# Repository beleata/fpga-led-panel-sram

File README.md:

# ICND1065L LED Panel: FPGA SRAM and RP2040 Pico

64x32 ICND1065L RGB LED panel drivers: Olimex iCE40HX1K FPGA with SRAM video
memory, and a YD-RP2040 / Raspberry Pi Pico PIO + DMA display implementation
with USB frame streaming. Wiring, initialization protocol, source, tests and
ready-to-flash firmware are included.

## Custom Controller PCB (Draft)

Самостоятелна двуслойна платка **88 x 46.1 mm** с RP2040, 8 MiB flash,
вертикална USB-C, RS-485 и W5500 Ethernet с вертикална RJ45.

**НЕ Е ГОТОВА ЗА ПРОИЗВОДСТВО.** Публикувани са схемата, 103 компонента,
ръчната подредба и пробно трасиране. След корекциите: 0 DRC нарушения,
но остава 1 неопроводена връзка QSPI_D1. Сигналната цялост и захранването
още не са квалифицирани. Това не променя статуса на работещия Pico модул.

- [PCB files, current status and documentation](hardware/pico-panel/README.md)
- [Пробно трасиране и ограничения](hardware/pico-panel/routing-trial/README_BG.md)

## RP2040 Pico

Потвърден работещ вариант с **YD-RP2040 2022-V1.3, 8 MiB flash**:
правилна геометрична фигура и стабилна картина. PIO и DMA изпълняват
проверената FPGA последователност при SCLK **1.5625 MHz**.

- [Свързване, компилиране и инструкции](pico/README_BG.md)
- [Готов firmware за YD-RP2040 8 MiB](pico/pico_panel.uf2)
- [Изходен код и тестове](pico/)

Добавен е USB CDC приемник с два RGB888 буфера във вътрешната SRAM на Pico.
PC декодира GIF и изпраща кадрите; Pico пази последния кадър при спиране
на изпращането. [USB видео: инструкции и протокол](pico/USB_VIDEO_BG.md).
Новият [USB firmware](pico/pico_panel_usb.uf2) е отделен от стария статичен UF2.
Измерени са 13,49 кадъра/s при 70 последователни кадъра, без PIO/DMA грешки;
визуалната проверка на новата анимация предстои.

## FPGA SRAM

Работещ проект за **Olimex iCE40HX1K-EVB**, RGB LED панел **64 x 32** с
ICND1065L драйвери и външна SRAM видео памет. Изображенията се изпращат от
компютър през OLIMEXINO-32U4 по UART **2 Mbaud**. Два SRAM буфера, CRC16 и
проверка чрез прочит след запис пазят активната картина при недовършен или
повреден пакет. Последната приета картина се показва без допълнителен трафик.

## Потвърдено На Реален Хардуер

- Правилна геометрия, цветове и стабилна статична картина.
- Приемане и показване на изображение от външния SRAM.
- Отхвърляне на грешна CRC и непълен кадър; безопасно повторение на пакет.
- Шест различни кадъра, 18 успешни прехвърляния: **3.16 кадъра/секунда**
  през текущия USB мост. Това не е физическият максимум на UART/SRAM.
- Потребителят потвърди картината и поиска непрекъсната анимация.

Проверки, хешове и ограничения: [video/VERIFICATION.md](video/VERIFICATION.md).
SRAM е енергозависима: след изключване или FPGA reset се връща началната
геометрична фигура, а не последният изпратен потребителски кадър.

## Бърз Старт

Текущата среда е Windows/PowerShell, Python 3.13, OSS CAD Suite в
`C:\oss-cad-suite`, Arduino AVR core 1.8.8. Инсталирайте Python зависимостите:

```powershell
python -m pip install -r requirements.txt
.\video\test.ps1
.\video\build.ps1
python program_panel.py video/video.bin --port COM18
python video/send_image.py --image C:\images\picture.png --port COM18
```

Картинката е 64 x 32; `--resize` разрешава преоразмеряване, `--rotate 180`
обръща изображението. Пиновете и безопасното свързване са описани в
[video/README_BG.md](video/README_BG.md). Не свързвайте 5 V към FPGA GPIO.
OLIMEXINO трябва да използва 3.3 V логически нива. GPIO1 пин 34 **не е земя**.
`HARDWARE.md` е историческа бележка и съдържа стари предположения; водещи
са актуалната документация, `.pcf` файловете и потвърдените резултати.

Анимация и спиране след текущия кадър:

```powershell
python video/animate.py --cycles 3
.\video\start_animation.ps1
.\video\stop_animation.ps1
```

Фоновата анимация държи COM18 отворен. Спрете я преди друга команда към
платката. Изпращането на изображения не презаписва FPGA flash.

## Съдържание

| Път | Предназначение |
|---|---|
| `video/` | Текущ SRAM драйвер, UART протокол, клиенти, тестове и bitstream |
| `pico/` | Потвърден RP2040 PIO/DMA статичен драйвер, UF2, свързване и тестове |
| `panel/` | Потвърдена стабилна статична версия за възстановяване |
| `link_test/` | UART диагностика и измервания на скоростта |
| `programmer-fw/` | OLIMEXINO USB/SPI/UART програматор и готов firmware |
| `backups/` | Работещи етапи, резервни копия и хешове |
| `logs/` | Запазени резултати от синтез, програмиране и тестове |
| `reference/` | Външни източници, фиксирани като Git submodules |
| `PANEL_PROTOCOL_BG.md` | Подробен протокол за управление на ICND1065L |
| `program_panel.py` | Двоен backup read, запис, проверка и CDONE |
| `iceprog.py` | Клиент за USB протокола на програматора |

Архивите `stable-panel-20260924.zip` и `video-sram-20260924.zip` пазят
самостоятелни работещи снимки на проекта. Текущите файлове извън архивите
може да съдържат по-нови помощни скриптове и документация.

## Референтни Източници

При клониране използвайте `git clone --recurse-submodules <repository-url>`.
За вече клонирано хранилище: `git submodule update --init --recursive`.
Основният FPGA build не изисква компилация на тези референтни проекти.

- [board707/DMD_STM32](https://github.com/board707/DMD_STM32),
  commit `398ec1d8636bce866709fbe9c3f0035c90645e7a`.
- [OLIMEX/iCE40HX1K-EVB](https://github.com/OLIMEX/iCE40HX1K-EVB),
  commit `91f3b5aff50258ddb40c021a21d4fd871633fc80`.
- [kingdo9/rpi-rgb-led-matrix_pwm_experiment](https://github.com/kingdo9/rpi-rgb-led-matrix_pwm_experiment),
  commit `5da13cb3b0d38d66bb5201f03704b5bef9e4446b`.

Външните проекти запазват собствените си лицензи и авторство. Това
хранилище не добавя нов общ лиценз върху техния код или хардуерни проекти.

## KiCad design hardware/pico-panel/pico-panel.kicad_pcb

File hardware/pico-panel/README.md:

# RP2040 ICND1065L Panel Controller PCB

**Development snapshot, 2026-09-25. NOT FOR MANUFACTURE.**

A custom two-layer 88 x 46.1 mm controller for the tested 64 x 32 ICND1065L
LED panel. Bare RP2040, 8 MiB flash, vertical USB-C, non-isolated RS-485,
W5500 Ethernet and a vertical HanRun HR963380AE integrated-magnetics jack.
KiCad 10.0.6 project, 103 components. The custom PCB has not been fabricated
or tested; the working YD-RP2040 module firmware is a separate result.

## Текущо състояние

- Основният `pico-panel.kicad_pcb` е последната ръчна подредба на потребителя,
  без писти. Не е презаписвана от генератора след ръчните корекции.
- `routing-trial/pico-panel.kicad_pcb` е отделно пробно трасиране със същите
  позиции и ориентации. Два слоя, 111 преходни отвора.
- Проверка на подредбата: 0 DRC нарушения, 285 неопроводени връзки.
- Проверка на пробното трасиране след локалните корекции: 0 DRC нарушения,
  **1 неопроводена връзка QSPI_D1: U2.2 към U1.55**.
- ERC на схемата: 0 нарушения. Това не заменя проверката на схемното решение.
- USB/Ethernet диференциалните трасета, земята и обратните токови пътища,
  кварцовите вериги, импулсният регулатор и защитите още изискват преглед.
- Няма производствено одобрение, Gerber release или потвърдени измервания.

## Файлове

| Файл / папка | Предназначение |
| --- | --- |
| `pico-panel.kicad_pro` | Основен KiCad проект |
| `pico-panel.kicad_sch` | Пълна схема |
| `pico-panel.kicad_pcb` | Запазена ръчна подредба, без писти |
| `Panel.pretty/`, `Panel.kicad_sym` | Локални footprints и символи |
| `parts.json`, `BOM.csv` | Компоненти, LCSC кодове, връзки и текущи позиции |
| `preview/schematic.pdf` | Актуален PDF на схемата |
| `preview/user-placement.png` | Актуална ръчна подредба |
| `routing-trial/` | Двата опита за трасиране, логове, DSN/SES и текущ резултат |
| `reports/` | ERC/DRC, netlist, проверки на конектора и исторически отчети |
| `reference/` | Използвани datasheets, чертежи и публичен CAD на конектора |
| `tools/` | Скриптове за генериране, проверки и обработка на пробния маршрут |

## Механика и свързване

- Размер 88 x 46.1 mm; два медни слоя; зададена дебелина 0.8 mm.
- J1 е женски 2 x 8, 2.54 mm, от долната страна, за ръчно запояване.
- Поглед отгоре: J1.1 е x=13.202, y=15.600 mm от горния ляв ъгъл.
  Пин 2 е вдясно, пин 3 отдолу. Тези координати не са променяни.
- Отделни +5 V/GND проводници захранват контролера от панела.
  USB VBUS не захранва контролера; за програмиране също са нужни панелните 5 V.
- GP2..GP13 са директни 3.3 V сигнали към панела. Буферите и R20..R31 (33 ohm)
  са премахнати по заявка на потребителя; 47 kohm pull-down резисторите остават.
- J3: +5 V/GND; J5: RS-485 A/B/GND. Неполяризирани 2.54 mm конектори.
- Ethernet не е PoE. Схемата е за общата средна точка на конкретния MagJack.

## Отваряне и възпроизвеждане

Клонирайте целия repository и отворете `pico-panel.kicad_pro` с KiCad 10.
Локалните библиотеки използват `${KIPRJMOD}`. За пробния маршрут отворете
директно `routing-trial/pico-panel.kicad_pcb`; той не заменя основната подредба.

Скриптовете са от Windows работната среда. Част от тях съдържат абсолютни
пътища до KiCad, Java и локалния каталог за компоненти; адаптирайте ги преди
стартиране на друга машина. `pcbnew` изисква Python средата на KiCad.

**Не изпълнявайте `build_pcb.py` или `apply_wide_placement.py` върху ръчно
редактирана платка:** те заменят подредбата. Генераторната подредба е по-стара
от последните ръчни корекции. Авторитетен е запазеният `.kicad_pcb` файл.

`routing-trial/README_BG.md` описва границите на теста и локалните корекции.
Скриптовете за миграции/корекции са еднократни операции, не общ build pipeline.

## Документация и история

- [Проектни решения и исторически варианти](DESIGN_BG.md)
- [Проверка на RJ45 footprint](ETHERNET_FOOTPRINT_BG.md)
- [Първоначална механична Ethernet проба](ETHERNET_OPTION_BG.md)
- [Проверен firmware за готовия Pico модул](../../pico/README_BG.md)

По-старите изображения в `preview/` и част от отчетите са от предишни размери
и по-малък брой елементи. Тази страница и текущите основни KiCad файлове
определят актуалното състояние. Локалните crash snapshots, editor lock files,
временни тестови схеми и дублиращи резервни копия не са публикувани.

Изтегленият файл `ABM8-25MHz.pdf` се оказа HTML страница, а не datasheet,
и е изключен от публикацията. Документацията и товарният капацитет на 25 MHz
кварца трябва да бъдат проверени допълнително преди производство.
Datasheets/CAD в `reference/` принадлежат на съответните производители.

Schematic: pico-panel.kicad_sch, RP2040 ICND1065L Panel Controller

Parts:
C1, C2: 15p; C_0603_1608Metric; LCSC C1644
C3, C22, C23, C25, C43, C47: 100n; C_0603_1608Metric; LCSC C14663
C4, C5, C6, C7, C8, C9, C10, C11, C12, C13, C14, C30, C31, C32, C33, C34, C35, C37: 100n; C_0402_1005Metric; LCSC C1525
C15, C16, C17: 1u; C_0603_1608Metric; LCSC C15849
C18, C36: 10u 16V; C_0805_2012Metric; LCSC C1713
C19, C24: 22u 10V; C_0805_2012Metric; LCSC C29277
C38, C39: 4.7u; C_0603_1608Metric; LCSC C19666
C40, C44: 10n; C_0603_1608Metric; LCSC C57112
C41, C42: 27p C0G; C_0603_1608Metric; LCSC C1656
C45, C46: 6.8n; C_0603_1608Metric; LCSC C84723
C48: 1n 1kV; C_1206_3216Metric; LCSC C1941
D1: STATUS green; LED_0805_2012Metric; LCSC C2297
D2: SS14; D_SMA; LCSC C2480
D4: SM712; SOT-23; LCSC C32677
F1: PTC 0.5A; Fuse_1206_3216Metric; LCSC C70076
FB1: 120R@100MHz 2A; L_0603_1608Metric; LCSC C14709
J1: PANEL BOTTOM 2x8; PinSocket_2x08_P2.54mm_Vertical
J2: USB-C VERTICAL H6.5; USB_C_SHOUHAN_TYPE-C_16PLT-H6.5_Vertical; LCSC C3151748
J3: PANEL POWER +5V GND; PinHeader_1x02_P2.54mm_Vertical
J4: SWD 3V3 GND CLK IO RUN; PinHeader_1x05_P2.54mm_Vertical
J5: RS485 A B GND; PinHeader_1x03_P2.54mm_Vertical
J6: HR963380AE MAGJACK; RJ45_HanRun_HR963380AE_Vertical; LCSC C19724763
JP1: TERM 120R; PinHeader_1x02_P2.54mm_Vertical
L1: 3.9u SWPA4030S3R9MT; L_Sunlord_SWPA4030S; LCSC C96899
R1, R3, R18, R62, R63: 10k; R_0603_1608Metric; LCSC C25804
R2, R4, R5: 1k; R_0603_1608Metric; LCSC C21190
R6, R7: 5.1k; R_0603_1608Metric; LCSC C23186
R8, R9: 27; R_0603_1608Metric; LCSC C25190
R10, R11, R12, R13: 100k; R_0603_1608Metric; LCSC C25803
R19: 120 0.25W; R_1206_3216Metric; LCSC C17909
R40, R41, R42, R43, R44, R45, R46, R47, R48, R49, R50, R51: 47k; R_0603_1608Metric; LCSC C25819
R60: 12.4k 1%; R_0402_1005Metric; LCSC C11692
R61: 1M; R_0603_1608Metric; LCSC C22935
R64, R65, R66, R67: 49.9 1%; R_0603_1608Metric; LCSC C23185
R68: 10; R_0603_1608Metric; LCSC C22859
R69, R70: 470; R_0603_1608Metric; LCSC C23179
SW1: BOOTSEL; SW_SPST_TL3342
SW2: RESET; SW_SPST_TL3342
U1: RP2040; QFN-56-1EP_7x7mm_P0.4mm_EP3.2x3.2mm; LCSC C2040
U2: W25Q64JVSSIQ; SOIC-8_5.3x5.3mm_P1.27mm; LCSC C179171
U3: USBLC6-2SC6; SOT-23-6; LCSC C7519
U4: AP63203WU-7; TSOT-23-6; LCSC C780769
U7: SN65HVD75DR; SOIC-8_3.9x4.9mm_P1.27mm; LCSC C57928
U8: W5500; LQFP-48_7x7mm_P0.5mm; LCSC C32843
Y1: ABM8-272-T3 12MHz; Crystal_SMD_3225-4Pin_3.2x2.5mm; LCSC C20625731
Y2: ABM8-25.000MHZ-D2Y-T; Crystal_SMD_3225-4Pin_3.2x2.5mm; LCSC C179643

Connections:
1V1: C13.1, C14.1, C15.1, U1.23 (DVDD), U1.45 (VREG_VOUT), U1.50 (DVDD)
3V3: C3.1, C4.1, C5.1, C6.1, C7.1, C8.1, C9.1, C10.1, C11.1, C12.1, C16.1, C19.1, C22.1, C24.1, C37.1, C38.1, FB1.1, J4.1, J6.12, J6.14, L1.2, R1.1, R3.1, R62.1, R63.1, U1.1 (IOVDD), U1.10 (IOVDD), U1.22 (IOVDD), U1.33 (IOVDD), U1.42 (IOVDD), U1.43 (ADC_AVDD), U1.44 (VREG_VIN), U1.48 (USB_VDD), U1.49 (IOVDD), U2.8 (VCC), U4.1 (FB), U7.8 (VCC), U8.28 (VDD), U8.43 (PMODE2), U8.44 (PMODE1), U8.45 (PMODE0)
BOOT_SW: R2.2, SW1.1
BUCK_BST: C23.1, U4.6 (BST)
BUCK_SW: C23.2, L1.1, U4.5 (SW)
CC1: J2.A5 (CC1), R6.1
CC2: J2.B5 (CC2), R7.1
CHASSIS: C48.1, J6.15
ETH_1V2: C40.1, U8.22 (1V2O)
ETH_ACT: R70.1, U8.27 (ACTLED)
ETH_ACT_K: J6.11, R70.2
ETH_AVDD: C30.1, C31.1, C32.1, C33.1, C34.1, C35.1, C36.1, FB1.2, R64.2, R65.2, R68.1, U8.4 (AVDD), U8.8 (AVDD), U8.11 (AVDD), U8.15 (AVDD), U8.17 (AVDD), U8.21 (AVDD)
ETH_CS: R63.2, U1.28 (GPIO17), U8.32 (~SCS)
ETH_CT: C47.1, J6.5, J6.6, R68.2
ETH_EXRES: R60.1, U8.10 (EXRES1)
ETH_INT: U1.32 (GPIO21), U8.36 (~INT)
ETH_J_RX_N: C46.2, J6.4
ETH_J_RX_P: C45.2, J6.3
ETH_LINK: R69.1, U8.25 (LINKLED)
ETH_LINK_K: J6.13, R69.2
ETH_MISO: U1.27 (GPIO16), U8.34 (MISO)
ETH_MOSI: U1.30 (GPIO19), U8.35 (MOSI)
ETH_RESET: C43.1, R62.2, U1.31 (GPIO20), U8.37 (~RST)
ETH_RX_BIAS: C44.1, R66.2, R67.2
ETH_RX_N: C46.1, R67.1, U8.5 (RXN)
ETH_RX_P: C45.1, R66.1, U8.6 (RXP)
ETH_SCK: U1.29 (GPIO18), U8.33 (SCLK)
ETH_TOCAP: C39.1, U8.20 (TOCAP)
ETH_TX_N: J6.2, R65.1, U8.1 (TXN)
ETH_TX_P: J6.1, R64.1, U8.2 (TXP)
ETH_XI: C41.1, R61.1, U8.30 (XI/CLKIN), Y2.1
ETH_XO: C42.1, R61.2, U8.31 (XO), Y2.3
GND: C1.2, C2.2, C3.2, C4.2, C5.2, C6.2, C7.2, C8.2, C9.2, C10.2, C11.2, C12.2, C13.2, C14.2, C15.2, C16.2, C17.2, C18.2, C19.2, C22.2, C24.2, C25.2, C30.2, C31.2, C32.2, C33.2, C34.2, C35.2, C36.2, C37.2, C38.2, C39.2, C40.2, C41.2, C42.2, C43.2, C44.2, C47.2, C48.2, D1.1 (K), D4.3 (common), J1.4, J1.8, J1.12, J1.16, J2.A1 (GND), J2.A12 (GND), J2.B1 (GND), J2.B12 (GND), J2.SH (SHIELD), J3.2, J4.2, J5.3, R6.2, R7.2, R11.2, R13.2, R18.2, R40.2, R41.2, R42.2, R43.2, R44.2, R45.2, R46.2, R47.2, R48.2, R49.2, R50.2, R51.2, R60.2, SW1.2, SW2.2, U1.19 (TESTEN), U1.57 (GND), U2.4 (GND), U3.2 (GND), U4.4 (GND), U7.5 (GND), U8.3 (AGND), U8.9 (AGND), U8.14 (AGND), U8.16 (AGND), U8.19 (AGND), U8.23 (RSVD), U8.29 (GND), U8.48 (AGND), Y1.2 (G), Y1.4 (G), Y2.2 (G), Y2.4 (G)
LED_A: D1.2 (A), R5.2
LED_STATUS: R5.1, U1.37 (GPIO25)
PANEL_5V: D2.2 (A), F1.2, R12.1
PANEL_5V_IN: F1.1, J3.1
PANEL_A: J1.9, R46.1, U1.11 (GPIO8)
PANEL_B: J1.10, R47.1, U1.12 (GPIO9)
PANEL_B1: J1.3, R42.1, U1.6 (GPIO4)
PANEL_B2: J1.7, R45.1, U1.9 (GPIO7)
PANEL_C: J1.11, R48.1, U1.13 (GPIO10)
PANEL_G1: J1.2, R41.1, U1.5 (GPIO3)
PANEL_G2: J1.6, R44.1, U1.8 (GPIO6)
PANEL_LAT: J1.14, R50.1, U1.15 (GPIO12)
PANEL_OE: J1.15, R51.1, U1.16 (GPIO13)
PANEL_R1: J1.1, R40.1, U1.4 (GPIO2)
PANEL_R2: J1.5, R43.1, U1.7 (GPIO5)
PANEL_SCLK: J1.13, R49.1, U1.14 (GPIO11)
PANEL_SENSE: R12.2, R13.1, U1.35 (GPIO23)
QSPI_CLK: U1.52 (QSPI_SCLK), U2.6 (CLK)
QSPI_CS: R1.2, R2.1, U1.56 (~QSPI_SS), U2.1 (~CS)
QSPI_D0: U1.53 (QSPI_SD0), U2.5 (DI/IO_{0})
QSPI_D1: U1.55 (QSPI_SD1), U2.2 (DO/IO_{1})
QSPI_D2: U1.54 (QSPI_SD2), U2.3 (~WP/IO_{2})
QSPI_D3: U1.51 (QSPI_SD3), U2.7 (~HOLD/~RESET/IO_{3})
RS485_A: D4.1 (A1), J5.1, R19.1, U7.6 (A)
RS485_B: D4.2 (A2), J5.2, JP1.2, U7.7 (B)
RS485_DIR: R18.1, U1.18 (GPIO15), U7.2 (~RE), U7.3 (DE)
RUN: J4.5, R3.2, SW2.1, U1.26 (RUN)
SWCLK: J4.3, U1.24 (SWCLK)
SWDIO: J4.4, U1.25 (SWDIO)
SYS_5V: C18.1, C25.1, D2.1 (K), U4.2 (EN), U4.3 (IN)
TERM: JP1.1, R19.2
UART_RX: U1.3 (GPIO1), U7.1 (RO)
UART_TX: U1.2 (GPIO0), U7.4 (DI)
USB_5V: C17.1, J2.A4 (VBUS), J2.A9 (VBUS), J2.B4 (VBUS), J2.B9 (VBUS), R10.1, U3.5 (VBUS)
USB_DM: J2.A7 (D-), J2.B7 (D-), R9.1, U3.3 (I/O2), U3.4 (I/O2)
USB_DM_MCU: R9.2, U1.46 (USB_DM)
USB_DP: J2.A6 (D+), J2.B6 (D+), R8.1, U3.1 (I/O1), U3.6 (I/O1)
USB_DP_MCU: R8.2, U1.47 (USB_DP)
USB_SENSE: R10.2, R11.1, U1.36 (GPIO24)
XIN: C1.1, U1.20 (XIN), Y1.1
XOUT: R4.1, U1.21 (XOUT)
XTAL_OUT: C2.1, R4.2, Y1.3

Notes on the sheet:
ETHERNET / W5500 / COMMON-CT MAGJACK / NO PoE
RP2040 / FLASH / CLOCK / DEBUG
USB-C / POWER
PANEL OUTPUTS: 3.3V, BOTTOM CONNECTOR
RS-485: NON-ISOLATED
REV A DRAFT - NOT FOR MANUFACTURE
GP2..13: direct 3.3V, no series resistors. GP14 unused; GP23 senses panel power. RS485: GP0 TX, GP1 RX, GP15 direction. Panel 5V required also for USB programming. J1 pin 1 = (13.202,15.600) mm from top-left, TOP VIEW. Verify mating height before fabrication.

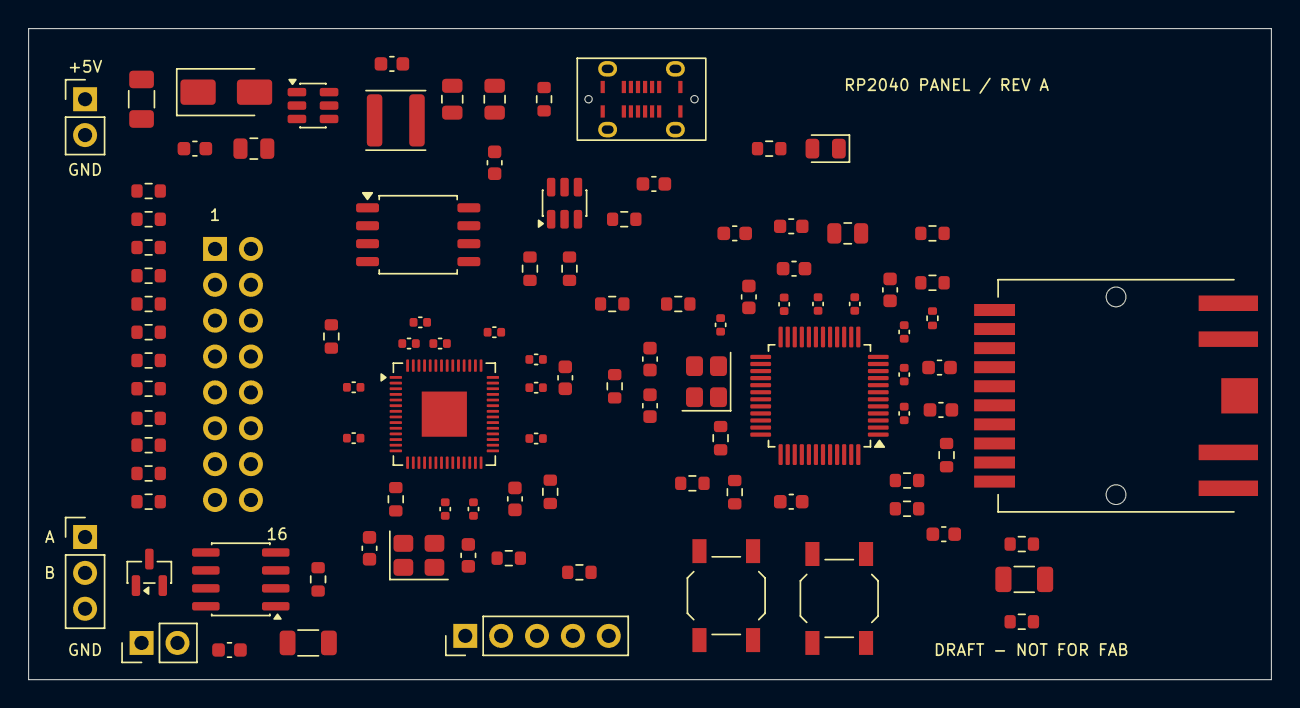
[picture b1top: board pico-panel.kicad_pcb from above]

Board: 2 copper layers, 88.0 x 46.1 mm, 103 parts (1 on the bottom side), 75 nets, no tracks yet.

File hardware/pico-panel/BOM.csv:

Reference,Value,Footprint,LCSC,Assembly,Side,X_mm,Y_mm,Rotation_deg
U1,RP2040,Package_DFN_QFN:QFN-56-1EP_7x7mm_P0.4mm_EP3.2x3.2mm,C2040,SMT,F,29.4375,27.3,0.0
U2,W25Q64JVSSIQ,Package_SO:SOIC-8_5.3x5.3mm_P1.27mm,C179171,SMT,F,27.5875,14.595,0.0
R1,10k,Resistor_SMD:R_0603_1608Metric,C25804,SMT,F,21.4375,21.8,90.0
R2,1k,Resistor_SMD:R_0603_1608Metric,C21190,SMT,F,39.0,38.5,0.0
SW1,BOOTSEL,Button_Switch_SMD:SW_SPST_TL3342,,HAND,F,49.4,40.15,90.0
SW2,RESET,Button_Switch_SMD:SW_SPST_TL3342,,HAND,F,57.4,40.35,90.0
R3,10k,Resistor_SMD:R_0603_1608Metric,C25804,SMT,F,34.0,37.5,0.0
Y1,ABM8-272-T3 12MHz,Crystal:Crystal_SMD_3225-4Pin_3.2x2.5mm,C20625731,SMT,F,27.6375,37.3,0.0
R4,1k,Resistor_SMD:R_0603_1608Metric,C21190,SMT,F,26.0,33.325,-90.0
C1,15p,Capacitor_SMD:C_0603_1608Metric,C1644,SMT,F,24.1375,36.8,90.0
C2,15p,Capacitor_SMD:C_0603_1608Metric,C1644,SMT,F,31.1375,37.3,90.0
C3,100n,Capacitor_SMD:C_0603_1608Metric,C14663,SMT,F,33.0,9.5,90.0
C4,100n,Capacitor_SMD:C_0402_1005Metric,C1525,SMT,F,23.02,25.4,0.0
C5,100n,Capacitor_SMD:C_0402_1005Metric,C1525,SMT,F,23.02,29.0,0.0
C6,100n,Capacitor_SMD:C_0402_1005Metric,C1525,SMT,F,29.5,34.02,90.0
C7,100n,Capacitor_SMD:C_0402_1005Metric,C1525,SMT,F,35.9375,29.025,0.0
C8,100n,Capacitor_SMD:C_0402_1005Metric,C1525,SMT,F,35.9375,25.425,0.0
C9,100n,Capacitor_SMD:C_0402_1005Metric,C1525,SMT,F,35.9375,23.425,0.0
C10,100n,Capacitor_SMD:C_0402_1005Metric,C1525,SMT,F,32.98,21.5,0.0
C11,100n,Capacitor_SMD:C_0402_1005Metric,C1525,SMT,F,29.1375,22.3,0.0
C12,100n,Capacitor_SMD:C_0402_1005Metric,C1525,SMT,F,26.9375,22.3,0.0
C13,100n,Capacitor_SMD:C_0402_1005Metric,C1525,SMT,F,31.5,34.02,90.0
C14,100n,Capacitor_SMD:C_0402_1005Metric,C1525,SMT,F,27.7375,20.8,0.0
C15,1u,Capacitor_SMD:C_0603_1608Metric,C15849,SMT,F,34.4375,33.3,90.0
C16,1u,Capacitor_SMD:C_0603_1608Metric,C15849,SMT,F,38.0,24.725,90.0
J4,SWD 3V3 GND CLK IO RUN,Connector_PinHeader_2.54mm:PinHeader_1x05_P2.54mm_Vertical,,HAND,F,30.92,43.0,90.0
R5,1k,Resistor_SMD:R_0603_1608Metric,C21190,SMT,F,52.4375,8.5,0.0
D1,STATUS green,LED_SMD:LED_0805_2012Metric,C2297,SMT,F,56.4375,8.5,180.0
J2,USB-C VERTICAL H6.5,Panel:USB_C_SHOUHAN_TYPE-C_16PLT-H6.5_Vertical,C3151748,SMT,F,43.4,5.0,0.0
R6,5.1k,Resistor_SMD:R_0603_1608Metric,C23186,SMT,F,42.175,13.5,180.0
R7,5.1k,Resistor_SMD:R_0603_1608Metric,C23186,SMT,F,36.5,5.0,90.0
U3,USBLC6-2SC6,Package_TO_SOT_SMD:SOT-23-6,C7519,SMT,F,37.95,12.3625,90.0
R8,27,Resistor_SMD:R_0603_1608Metric,C25190,SMT,F,35.5,17.0,-90.0
R9,27,Resistor_SMD:R_0603_1608Metric,C25190,SMT,F,38.3,17.0,-90.0
C17,1u,Capacitor_SMD:C_0603_1608Metric,C15849,SMT,F,44.275,11.0,0.0
R10,100k,Resistor_SMD:R_0603_1608Metric,C25803,SMT,F,41.325,19.5,0.0
R11,100k,Resistor_SMD:R_0603_1608Metric,C25803,SMT,F,46.0,19.5,0.0
J3,PANEL POWER +5V GND,Connector_PinHeader_2.54mm:PinHeader_1x02_P2.54mm_Vertical,,HAND,F,4.0,5.0,0.0
F1,PTC 0.5A,Fuse:Fuse_1206_3216Metric,C70076,SMT,F,8.0,5.0,90.0
D2,SS14,Diode_SMD:D_SMA,C2480,SMT,F,14.0,4.5,0.0
U4,AP63203WU-7,Package_TO_SOT_SMD:TSOT-23-6,C780769,SMT,F,20.1375,5.45,0.0
C18,10u 16V,Capacitor_SMD:C_0805_2012Metric,C1713,SMT,F,15.95,8.5,180.0
C19,22u 10V,Capacitor_SMD:C_0805_2012Metric,C29277,SMT,F,30.0,5.0,90.0
L1,3.9u SWPA4030S3R9MT,Inductor_SMD:L_Sunlord_SWPA4030S,C96899,SMT,F,26.0,6.5,0.0
C23,100n,Capacitor_SMD:C_0603_1608Metric,C14663,SMT,F,25.725,2.5,0.0
C24,22u 10V,Capacitor_SMD:C_0805_2012Metric,C29277,SMT,F,33.0,5.0,90.0
C25,100n,Capacitor_SMD:C_0603_1608Metric,C14663,SMT,F,11.775,8.5,0.0
R12,100k,Resistor_SMD:R_0603_1608Metric,C25803,SMT,F,36.9375,32.8,90.0
R13,100k,Resistor_SMD:R_0603_1608Metric,C25803,SMT,F,47.0,32.2,0.0
J1,PANEL BOTTOM 2x8,Connector_PinSocket_2.54mm:PinSocket_2x08_P2.54mm_Vertical,,HAND,B,13.202,15.6,180.0
R40,47k,Resistor_SMD:R_0603_1608Metric,C25819,SMT,F,8.5,11.5,0.0
R41,47k,Resistor_SMD:R_0603_1608Metric,C25819,SMT,F,8.5,13.5,0.0
R42,47k,Resistor_SMD:R_0603_1608Metric,C25819,SMT,F,8.5,15.5,0.0
R43,47k,Resistor_SMD:R_0603_1608Metric,C25819,SMT,F,8.5,17.5,0.0
R44,47k,Resistor_SMD:R_0603_1608Metric,C25819,SMT,F,8.5,19.5,0.0
R45,47k,Resistor_SMD:R_0603_1608Metric,C25819,SMT,F,8.5,21.5,0.0
R46,47k,Resistor_SMD:R_0603_1608Metric,C25819,SMT,F,8.5,23.5,0.0
R47,47k,Resistor_SMD:R_0603_1608Metric,C25819,SMT,F,8.5,25.5,0.0
R48,47k,Resistor_SMD:R_0603_1608Metric,C25819,SMT,F,8.5,27.6,0.0
R49,47k,Resistor_SMD:R_0603_1608Metric,C25819,SMT,F,8.5,29.5,0.0
R50,47k,Resistor_SMD:R_0603_1608Metric,C25819,SMT,F,8.5,31.5,0.0
R51,47k,Resistor_SMD:R_0603_1608Metric,C25819,SMT,F,8.5,33.5,0.0
U7,SN65HVD75DR,Package_SO:SOIC-8_3.9x4.9mm_P1.27mm,C57928,SMT,F,15.025,39.0,180.0
C22,100n,Capacitor_SMD:C_0603_1608Metric,C14663,SMT,F,14.225,44.0,0.0
R18,10k,Resistor_SMD:R_0603_1608Metric,C25804,SMT,F,20.5,39.0,90.0
D4,SM712,Package_TO_SOT_SMD:SOT-23,C32677,SMT,F,8.55,38.5,90.0
J5,RS485 A B GND,Connector_PinHeader_2.54mm:PinHeader_1x03_P2.54mm_Vertical,,HAND,F,4.0,36.0,0.0
R19,120 0.25W,Resistor_SMD:R_1206_3216Metric,C17909,SMT,F,19.8,43.5,0.0
JP1,TERM 120R,Connector_PinHeader_2.54mm:PinHeader_1x02_P2.54mm_Vertical,,HAND,F,8.0,43.5,90.0
U8,W5500,Package_QFP:LQFP-48_7x7mm_P0.5mm,C32843,SMT,F,56.0,26.0,180.0
J6,HR963380AE MAGJACK,Panel:RJ45_HanRun_HR963380AE_Vertical,C19724763,SMT,F,77.0,26.0,-90.0
FB1,120R@100MHz 2A,Inductor_SMD:L_0603_1608Metric,C14709,SMT,F,54.0,14.0,0.0
C30,100n,Capacitor_SMD:C_0402_1005Metric,C1525,SMT,F,62.0,27.25,90.0
C31,100n,Capacitor_SMD:C_0402_1005Metric,C1525,SMT,F,62.0,24.5,90.0
C32,100n,Capacitor_SMD:C_0402_1005Metric,C1525,SMT,F,62.0,21.48,90.0
C33,100n,Capacitor_SMD:C_0402_1005Metric,C1525,SMT,F,58.5,19.5,90.0
C34,100n,Capacitor_SMD:C_0402_1005Metric,C1525,SMT,F,55.9,19.5,90.0
C35,100n,Capacitor_SMD:C_0402_1005Metric,C1525,SMT,F,53.5,19.52,90.0
C36,10u 16V,Capacitor_SMD:C_0805_2012Metric,C1713,SMT,F,58.0,14.5,0.0
C37,100n,Capacitor_SMD:C_0402_1005Metric,C1525,SMT,F,49.0,20.98,90.0
C38,4.7u,Capacitor_SMD:C_0603_1608Metric,C19666,SMT,F,50.0,14.5,0.0
C39,4.7u,Capacitor_SMD:C_0603_1608Metric,C19666,SMT,F,54.2,17.0,0.0
C40,10n,Capacitor_SMD:C_0603_1608Metric,C57112,SMT,F,51.0,19.0,90.0
R60,12.4k 1%,Resistor_SMD:R_0402_1005Metric,C11692,SMT,F,64.0,20.51,90.0
Y2,ABM8-25.000MHZ-D2Y-T,Crystal:Crystal_SMD_3225-4Pin_3.2x2.5mm,C179643,SMT,F,48.0,25.0,90.0
C41,27p C0G,Capacitor_SMD:C_0603_1608Metric,C1656,SMT,F,44.0,23.4,90.0
C42,27p C0G,Capacitor_SMD:C_0603_1608Metric,C1656,SMT,F,44.0,26.7,90.0
R61,1M,Resistor_SMD:R_0603_1608Metric,C22935,SMT,F,41.5,25.325,-90.0
R62,10k,Resistor_SMD:R_0603_1608Metric,C25804,SMT,F,50.0,32.825,-90.0
C43,100n,Capacitor_SMD:C_0603_1608Metric,C14663,SMT,F,54.0,33.5,0.0
R63,10k,Resistor_SMD:R_0603_1608Metric,C25804,SMT,F,49.0,29.0,90.0
R64,49.9 1%,Resistor_SMD:R_0603_1608Metric,C23185,SMT,F,62.2,32.0,0.0
R65,49.9 1%,Resistor_SMD:R_0603_1608Metric,C23185,SMT,F,62.2,34.0,0.0
R66,49.9 1%,Resistor_SMD:R_0603_1608Metric,C23185,SMT,F,64.0,18.0,0.0
R67,49.9 1%,Resistor_SMD:R_0603_1608Metric,C23185,SMT,F,64.0,14.5,0.0
C44,10n,Capacitor_SMD:C_0603_1608Metric,C57112,SMT,F,61.0,18.5,90.0
C45,6.8n,Capacitor_SMD:C_0603_1608Metric,C84723,SMT,F,64.599999,27.0,0.0
C46,6.8n,Capacitor_SMD:C_0603_1608Metric,C84723,SMT,F,64.5,24.0,0.0
R68,10,Resistor_SMD:R_0603_1608Metric,C22859,SMT,F,65.0,30.2,90.0
C47,100n,Capacitor_SMD:C_0603_1608Metric,C14663,SMT,F,64.8,35.8,0.0
R69,470,Resistor_SMD:R_0603_1608Metric,C23179,SMT,F,70.325,36.5,0.0
R70,470,Resistor_SMD:R_0603_1608Metric,C23179,SMT,F,70.325,42.0,0.0
C48,1n 1kV,Capacitor_SMD:C_1206_3216Metric,C1941,SMT,F,70.5,39.0,180.0

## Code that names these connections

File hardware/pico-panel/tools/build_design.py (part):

"""Generate the schematic and explicit pin-net manifest. Run with KiCad Python."""
from pathlib import Path
import json
import re
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     '25':'ETH_LINK','27':'ETH_ACT','28':'3V3','29':'GND','30':'ETH_XI','31':'ETH_XO',
     '32':'ETH_CS','33':'ETH_SCK','34':'ETH_MISO','35':'ETH_MOSI','36':'ETH_INT','37':'ETH_RESET',
     '43':'3V3','44':'3V3','45':'3V3'}
eth.update({str(pin):'ETH_AVDD' for pin in (4,8,11,15,17,21)})
eth.update({str(pin):'GND' for pin in (3,9,14,16,19,48)})
add('U8','W5500',W5500,'Package_QFP:LQFP-48_7x7mm_P0.5mm',eth,(160,670),(34,39),'C32843')
add('J6','HR963380AE MAGJACK','Connector_Generic:Conn_01x15',
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    return pos

add('FB1','120R@100MHz 2A','Device:FerriteBead','Inductor_SMD:L_0603_1608Metric',
    {'1':'3V3','2':'ETH_AVDD'},loc(),(24,35),'C14709')
for i,pin in enumerate((4,8,11,15,17,21),30):
    c(f'C{i}','100n','ETH_AVDD','GND',loc(),(20+i-30,35),'C1525',fp='Capacitor_SMD:C_0402_1005Metric')
c('C36','10u 16V','ETH_AVDD','GND',loc(),(23,37),'C1713',fp='Capacitor_SMD:C_0805_2012Metric')
c('C37','100n','3V3','GND',loc(),(23,39),'C1525',fp='Capacitor_SMD:C_0402_1005Metric')
c('C38','4.7u','3V3','GND',loc(),(23,41),'C19666')
c('C39','4.7u','ETH_TOCAP','GND',loc(),(27,41),'C19666')
c('C40','10n','ETH_1V2','GND',loc(),(27,43),'C57112')
r('R60','12.4k 1%','ETH_EXRES','GND',loc(),(27,35),'C11692',fp='Resistor_SMD:R_0402_1005Metric')
add('Y2','ABM8-25.000MHZ-D2Y-T','Device:Crystal_GND24','Crystal:Crystal_SMD_3225-4Pin_3.2x2.5mm',
    {'1':'ETH_XI','2':'GND','3':'ETH_XO','4':'GND'},loc(),(25,40),'C179643')
c('C41','27p C0G','ETH_XI','GND',loc(),(22,40),'C1656')
c('C42','27p C0G','ETH_XO','GND',loc(),(28,40),'C1656')
r('R61','1M','ETH_XI','ETH_XO',loc(),(25,37),'C22935')
r('R62','10k','3V3','ETH_RESET',loc(),(26,30))
c('C43','100n','ETH_RESET','GND',loc(),(28,30))
r('R63','10k','3V3','ETH_CS',loc(),(26,28))
for ref,net in [('R64','ETH_TX_P'),('R65','ETH_TX_N')]:
    r(ref,'49.9 1%',net,'ETH_AVDD',loc(),(39,29 if ref=='R64' else 31),'C23185')
for ref,net in [('R66','ETH_RX_P'),('R67','ETH_RX_N')]:
    r(ref,'49.9 1%',net,'ETH_RX_BIAS',loc(),(39,33 if ref=='R66' else 35),'C23185')
c('C44','10n','ETH_RX_BIAS','GND',loc(),(39,37),'C57112')
c('C45','6.8n','ETH_RX_P','ETH_J_RX_P',loc(),(41,31),'C84723')
c('C46','6.8n','ETH_RX_N','ETH_J_RX_N',loc(),(41,33),'C84723')
r('R68','10','ETH_AVDD','ETH_CT',loc(),(41,28),'C22859')
c('C47','100n','ETH_CT','GND',loc(),(44,28))
r('R69','470','ETH_LINK','ETH_LINK_K',loc(),(43,44),'C23179')
r('R70','470','ETH_ACT','ETH_ACT_K',loc(),(47,44),'C23179')
c('C48','1n 1kV','CHASSIS','GND',loc(),(52,24),'C1941',fp='Capacitor_SMD:C_1206_3216Metric')
s.text('ETHERNET / W5500 / COMMON-CT MAGJACK / NO PoE',(25,595),size=3)

# Dedicated supply flags represent the passive diode-fed rails, not hidden ERC suppression.
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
